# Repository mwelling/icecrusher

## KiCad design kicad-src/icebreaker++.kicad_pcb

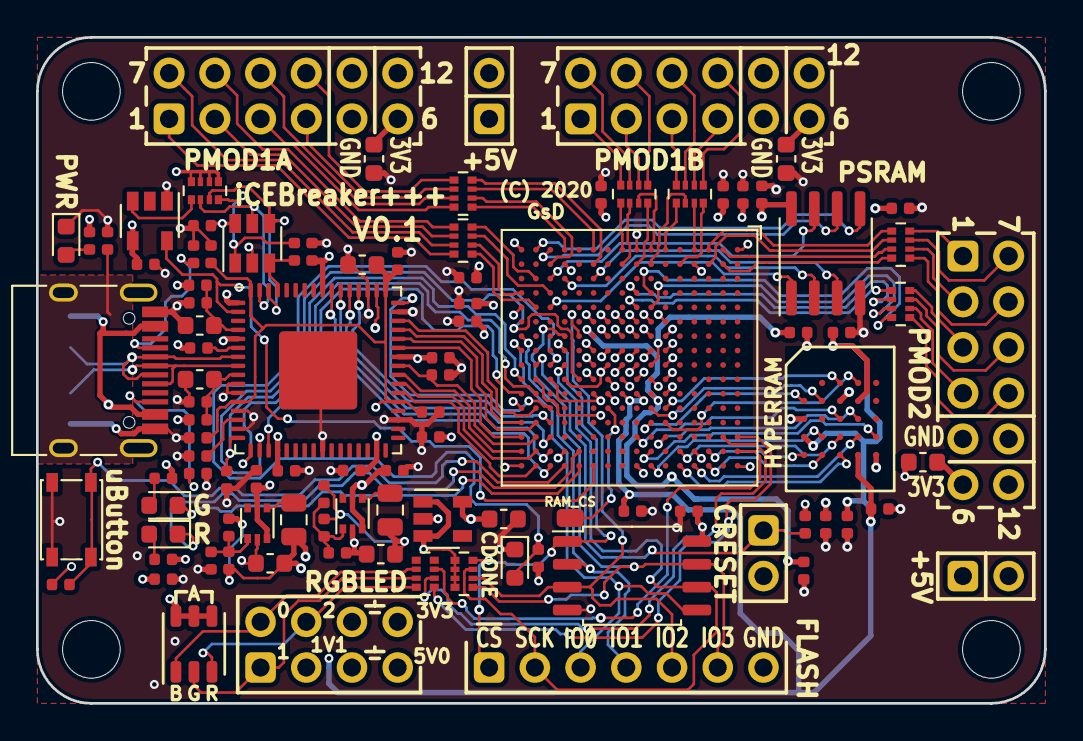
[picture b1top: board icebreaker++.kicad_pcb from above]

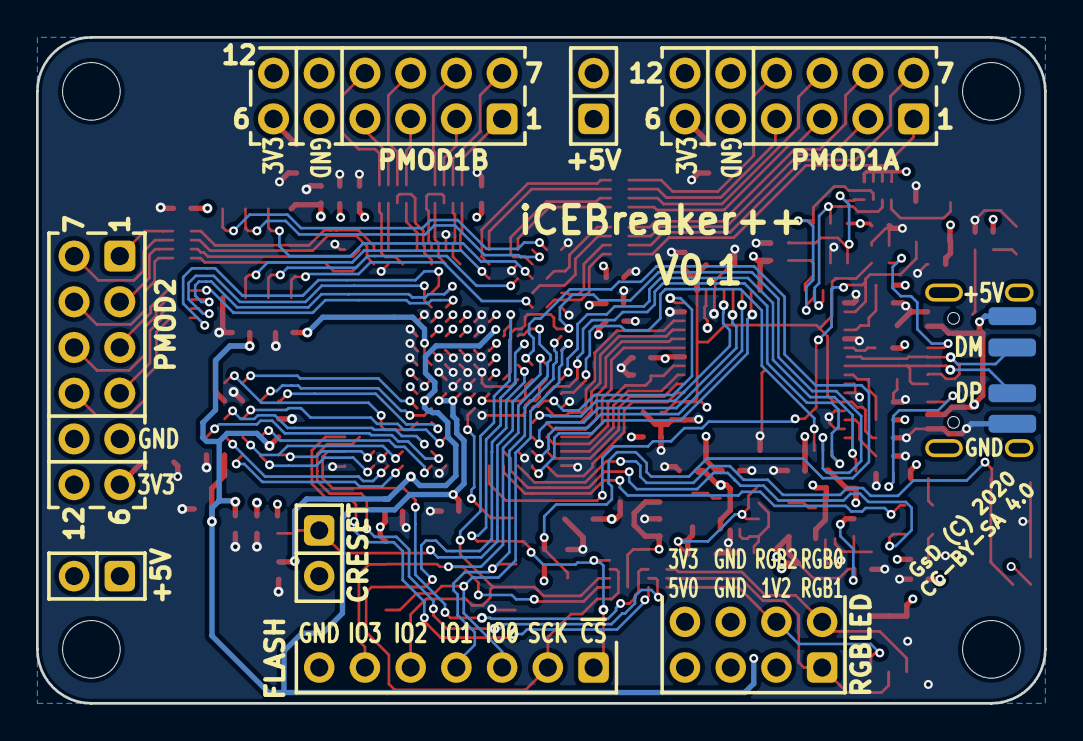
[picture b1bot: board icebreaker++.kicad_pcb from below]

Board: 4 copper layers, 56.0 x 37.0 mm, 104 parts (4 on the bottom side), 130 nets.

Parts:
C1, C4, C10, C12, C13, C14, C16, C17, C18, C19, C20, C21, C22: 100n; C_0402_1005Metric
C2, C3, C5, C8, C11, C35, C36, C37, C38, C39, C40, C41, C42, C43: 0.1uF; C_0402_1005Metric
C6, C7, C9: 4u7; C_0603_1608Metric
C15, C23: 4.7uF; C_0402_1005Metric
C24, C28, C29: 10uF; C_0603_1608Metric
C25, C30, C31: 1uF; C_0402_1005Metric
C26, C27: 6.8pF; C_0402_1005Metric
C32, C33, C34: DNP; C_0603_1608Metric
D1, D4: GRN; LED_0603_1608Metric
D3: BLU; LED_0603_1608Metric
D5: RED; LED_0603_1608Metric
D11: LED_RGB; LED_Cree_PLCC6_3.4x3.4mm
J20: Flash; PinHeader_1x07_P2.54mm_Vertical
J21, J23, J27: PMOD; PMOD_Angled_2x06
J22, J26: 5V AUX; PinHeader_2x01_P2.54mm_Vertical
J24: USB_C_Receptacle_USB2.0; USB_C_Receptacle_HRO_TYPE-C-31-M-12
J25: RGB Led; PinHeader_2x04_P2.54mm_Vertical
J28: CRESET; PinHeader_2x01_P2.54mm_Vertical
L1, L2: 600; L_0402_1005Metric
L3, L4: 2.2uH; L_0805_2012Metric
P2, P3, P4, P5: UP; PAD_SMD_1x2.65
P6: RAM_CS; PAD_SMD_1x1.5
R1: 1M; R_0402_1005Metric
R2, R11: 10k; R_Array_Convex_4x0402
R3, R4, R7, R16, R17, R18, R27: 33R; R_Array_Convex_4x0402
R5, R14, R15: 330E; R_0402_1005Metric
R6, R12: 2k2; R_0402_1005Metric
R8: 12k; R_0402_1005Metric
R9, R13, R19, R25: 10k; R_0402_1005Metric
R10: 210k; R_0402_1005Metric
R20: 1k; R_0402_1005Metric
R21, R22: 5.1k; R_0402_1005Metric
R23: 47k; R_0402_1005Metric
R24: 84k5; R_0402_1005Metric
R26: 100k; R_0402_1005Metric
SW1: TACT; SW_SPST_PTS810
U1: 93C46B-SOT-23-6; SOT-23-6
U2: FT2232H; QFN-64-1EP_9x9mm_P0.5mm_EP4.35x4.35mm
U3: W25Q32JVSS; SOIC-8_5.23x5.23mm_P1.27mm
U4, U5: TLV62569DRL; SOT-666
U6: TLV713285PDBV; SOT-23-5
U7: 12MHz; SOT-23-5
U8: ECP5U-12-CABGA256; BGA-256_14.0x14.0mm_Layout16x16_P0.8mm_Ball0.45mm_Pad0.32mm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
U9: LY68L6400SLIT; SOIC-8_3.9x4.9mm_P1.27mm
U10: IS66WVH16M8ALL; BGA-24_8.0x6.0mm_Layout5x5_P0.8mm_Pad0.35mm_NSMD

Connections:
+1V1: C27.1, C29.1, C31.1, C35.1, C36.1, C37.1, C38.1, L4.2, R24.2, U8.G6 (VCC[6]), U8.G7 (VCC[6]), U8.G9 (VCC[6]), U8.L8 (VCC[6]), U8.L9 (VCC[6]), U8.L10 (VCC[6])
+1V8: C7.1, C8.1, C10.1, C14.1, C16.1, C17.1, C40.1, C41.1, C42.1, U2.12 (VCORE), U2.37 (VCORE), U2.49 (VREGOUT), U2.64 (VCORE), U8.H11 (VCCIO2[2]), U8.J11 (VCCIO2[2]), U10.B4 (VCC), U10.D1 (VCCQ), U10.E4 (VCCQ)
+2V5: C24.1, C25.1, U6.5 (OUT), U8.G11 (VCCAUX[2]), U8.L7 (VCCAUX[2])
+3V3: C1.1, C2.1, C3.1, C4.1, C5.1, C11.1, C18.1, C19.1, C20.1, C21.1, C22.1, C26.1, C28.1, C30.1, C32.2, C33.2, C34.2, C39.1, C43.1, D11.4 (BA), D11.5 (GA), D11.6 (RA), J21.6, J21.12, J23.6, J23.12, J25.8, J27.6, J27.12, L1.1, L2.1, L3.2, R2.5, R2.6, R2.7, R2.8, R5.1, R9.2, R10.2, R11.1, R11.2, R11.3, R11.4, R12.1, R13.2, R14.2, R15.2, R19.1, U1.6 (VCC), U2.20 (VCCIO), U2.31 (VCCIO), U2.42 (VCCIO), U2.50 (VREGIN), U2.56 (VCCIO), U3.8 (VCC), U6.1 (IN), U6.3 (EN), U7.4 (VDD), U8.F10 (VCCIO1[2]), U8.F11 (VCCIO1[2]), U8.H6 (VCCIO7[2]), U8.H7 (VCCIO7[2]), U8.J6 (VCCIO6[2]), U8.J7 (VCCIO6[2]), U8.K11 (VCCIO3[2]), U8.L6 (VCCIO8), U8.L11 (VCCIO3[2]), U8.P10 (CFG_1), U9.8 (VCC)
+5V: C15.1, C23.1, J22.1, J24.A4 (VBUS), J24.A9 (VBUS), J24.B4 (VBUS), J24.B9 (VBUS), J25.7, J26.1, P2.1 (PAD), U4.3 (VIN), U4.5 (EN), U5.3 (VIN), U5.5 (EN)
/DONE: D3.2 (A), R12.2, U8.P9 (DONE)
/FLASH_CS: J20.1, R11.8, U3.1 (~CS), U8.N8 (PB15A/+/HOLDN/DI/BUSY/CSSPIN/CEN)
/FLASH_MISO|IO1: J20.4, U3.2 (DO(IO1)), U8.T7 (PB11A/+/D1/MISO/IO1)
/FLASH_MOSI|IO0: J20.3, U3.5 (DI(IO0)), U8.T8 (PB11B/-/D0/MOSI/IO0)
/FLASH_SCK: J20.2, R11.7, U3.6 (CLK), U8.N9 (CCLK/MCLK/SCK)
/FLASH_~HLD~|~RST~|IO3: J20.6, R11.5, U3.7 (IO3), U8.N7 (PB9A/+/D3/IO3)
/FLASH_~WP~|IO2: J20.5, R11.6, U3.3 (IO2), U8.M7 (PB9B/-/D2/IO2)
/FTDI_CLK: U2.2 (OSCI), U7.5 (OUT), U8.L16 (PR26A/+/PCLKT3_1/HS/RDQ32)
/JTAG_TCK: R20.1, U2.16 (ADBUS0), U8.T10 (TCK)
/JTAG_TDI: U2.17 (ADBUS1), U8.R11 (TDI)
/JTAG_TDO: U2.18 (ADBUS2), U8.M10 (TDO)
/JTAG_TMS: U2.19 (ADBUS3), U8.T11 (TMS)
/PMODS/P1A1: R16.5, U8.R5 (PL44A/+/HS/LDQS44)
/PMODS/P1A1x: J23.1, R16.4
/PMODS/P1A2: R16.7, U8.P4 (PL41A/+/HS/LDQ44)
/PMODS/P1A2x: J23.2, R16.2
/PMODS/P1A3: R3.5, U8.N1 (PL32A/+/HS/LDQS32)
/PMODS/P1A3x: J23.3, R3.4
/PMODS/P1A4: R3.7, U8.L1 (PL26A/+/PCLKT6_1/HS/LDQ32)
/PMODS/P1A4x: J23.4, R3.2
/PMODS/P1A7: R16.6, U8.T4 (PL44B/-/HS/LDQSN44)
/PMODS/P1A7x: J23.7, R16.3
/PMODS/P1A8: R16.8, U8.R3 (PL41B/-/HS/LDQ44)
/PMODS/P1A8x: J23.8, R16.1
/PMODS/P1A9: R3.6, U8.P2 (PL32B/-/HS/LDQSN32)
/PMODS/P1A9x: J23.9, R3.3
/PMODS/P1A10: R3.8, U8.L2 (PL26B/-/PCLKC6_1/HS/LDQ32)
/PMODS/P1A10x: J23.10, R3.1
/PMODS/P1B1: R4.1, U8.J1 (PL23A/+/PCLKT7_1/HS/LDQ20)
/PMODS/P1B1x: J27.1, R4.8
/PMODS/P1B2: R4.3, U8.G1 (PL20A/+/GR_PCLK7_1/HS/LDQS20)
/PMODS/P1B2x: J27.2, R4.6
/PMODS/P1B3: R17.1, U8.F1 (PL14A/+/HS/LDQ20)
/PMODS/P1B3x: J27.3, R17.8
/PMODS/P1B4: R17.3, U8.D1 (PL8A/+/HS/LDQS8)
/PMODS/P1B4x: J27.4, R17.6
/PMODS/P1B7: R4.2, U8.J2 (PL23B/-/PCLKC7_1/HS/LDQ20)
/PMODS/P1B7x: J27.7, R4.7
/PMODS/P1B8: R4.4, U8.H2 (PL20B/-/HS/LDQSN20)
/PMODS/P1B8x: J27.8, R4.5
/PMODS/P1B9: R17.2, U8.G2 (PL14B/-/HS/LDQ20)
/PMODS/P1B9x: J27.9, R17.7
/PMODS/P1B10: R17.4, U8.E2 (PL8B/-/HS/LDQSN8)
/PMODS/P1B10x: J27.10, R17.5
/PMODS/P2_1: R7.1, U8.C1 (PL5A/+/HS/LDQ8)
/PMODS/P2_1x: J21.1, R7.8
/PMODS/P2_2: R7.3, U8.B1 (PL2A/+/HS/LDQ8)
/PMODS/P2_2x: J21.2, R7.6
/PMODS/P2_3: R18.1, U8.H5 (PL17A/+/HS/LDQ20)
/PMODS/P2_3x: J21.3, R18.8
/PMODS/P2_4: R18.3, U8.G5 (PL11A/+/HS/LDQ8)
/PMODS/P2_4x: J21.4, R18.6
/PMODS/P2_7: R7.2, U8.C2 (PL5B/-/HS/LDQ8)
/PMODS/P2_7x: J21.7, R7.7
/PMODS/P2_8: R7.4, U8.B2 (PL2B/-/HS/LDQ8)
/PMODS/P2_8x: J21.8, R7.5
/PMODS/P2_9: R18.2, U8.H4 (PL17B/-/HS/LDQ20)
/PMODS/P2_9x: J21.9, R18.7
/PMODS/P2_10: R18.4, U8.G4 (PL11B/-/HS/LDQ8)
/PMODS/P2_10x: J21.10, R18.5
/PMODS/RAM_CLK: U8.P1 (PL35A/+/HS/LDQ32), U9.6 (CLK)
/PMODS/RAM_CS: U8.P5 (PL47D/-/LLC_GPLL0C_IN/LDQ44), U9.1 (~CS)
/PMODS/RAM_IO0: U8.R1 (PL35B/-/VREF1_6/HS/LDQ32), U9.5 (DI(IO0))
/PMODS/RAM_IO1: U8.N3 (PL35D/-/LDQ32), U9.2 (DO(IO1))
/PMODS/RAM_IO2: U8.L3 (PL32C/+/LDQ32), U9.3 (IO2)
/PMODS/RAM_IO3: U8.P3 (PL38B/-/HS/LDQ44), U9.7 (IO3)
/PROGRAMn: J28.1, R19.2, U8.R9 (PROGRAMN)
/RAM/HRAM_CLK: U8.G12 (PR11A/+/HS/RDQ8), U10.B2 (CK)
/RAM/HRAM_CLK#: U8.G13 (PR11B/-/HS/RDQ8), U10.B1 (CK#)
/RAM/HRAM_CS: U8.F12 (PR8D/-/RDQ8), U10.A3 (CS#)
/RAM/HRAM_DQ0: U8.E15 (PR8B/-/HS/RDQSN8), U10.D3 (DQ0)
/RAM/HRAM_DQ1: U8.G16 (PR20A/+/GR_PCLK2_1/HS/RDQS20), U10.D2 (DQ1)
/RAM/HRAM_DQ2: U8.F14 (PR5D/-/RDQ8), U10.C4 (DQ2)
/RAM/HRAM_DQ3: U8.D16 (PR8A/+/HS/RDQS8), U10.D4 (DQ3)
/RAM/HRAM_DQ4: U8.G15 (PR14B/-/HS/RDQ20), U10.D5 (DQ4)
/RAM/HRAM_DQ5: U8.E16 (PR11D/-/RDQ8), U10.E3 (DQ5)
/RAM/HRAM_DQ6: U8.C16 (PR5A/+/HS/RDQ8), U10.E2 (DQ6)
/RAM/HRAM_DQ7: U8.C15 (PR5B/-/HS/RDQ8), U10.E1 (DQ7)
/RAM/HRAM_RST: U8.F13 (PR8C/+/RDQ8), U10.A4 (RESET#)
/RAM/HRAM_RWDS: U8.H14 (PR14D/-/RDQ20), U10.C3 (RWDS)
/RAM_CS: P6.1 (PAD), U8.K12 (PR29B/-/HS/RDQ32)
/USB_DM: J24.A7 (D-), J24.B7 (D-), P3.1 (PAD), U2.7 (DM)
/USB_DP: J24.A6 (D+), J24.B6 (D+), P4.1 (PAD), U2.8 (DP)
/shield: J24.S1 (SHIELD), R1.2
/xFIFO_D0: U2.38 (BDBUS0), U8.R16 (PR35B/-/VREF1_3/HS/RDQ32)
/xFIFO_D1: U2.39 (BDBUS1), U8.R15 (PR38C/+/RDQ44)
/xFIFO_D2: U2.40 (BDBUS2), U8.T15 (PR38D/-/RDQ44)
/xFIFO_D3: R25.1, U2.41 (BDBUS3), U8.R14 (PR41B/-/HS/RDQ44)
/xFIFO_D4: U2.43 (BDBUS4), U8.T14 (PR41D/-/RDQ44)
/xFIFO_D5: U2.44 (BDBUS5), U8.R13 (PR41C/+/RDQ44)
/xFIFO_D6: U2.45 (BDBUS6), U8.T13 (PR44B/-/HS/RDQSN44)
/xFIFO_D7: U2.46 (BDBUS7), U8.R12 (PR44A/+/HS/RDQS44)
/xFIFO_WKUP: U2.55 (BCBUS4), U8.P16 (PR35A/+/HS/RDQ32)
/xFIFO_~RD: U2.53 (BCBUS2), U8.P14 (PR38B/-/HS/RDQ44)
/xFIFO_~RXF: U2.48 (BCBUS0), U8.P12 (PR47D/-/LRC_GPLL0C_IN/RDQ44)
/xFIFO_~TXE: U2.52 (BCBUS1), U8.P13 (PR41A/+/HS/RDQ44)
/xFIFO_~WR: U2.54 (BCBUS3), U8.P15 (PR32B/-/HS/RDQSN32)
/~BUTTON: R13.1, SW1.1, U8.N16 (PR32A/+/HS/RDQS32)
/~LEDG: D4.1 (K), U8.M16 (PR26C/+/PCLKT3_0/RDQ32)
/~LEDR: D5.1 (K), U8.M15 (PR26D/-/PCLKC3_0/RDQ32)
/~LED_RGB0: D11.1 (RK), J25.2, R27.2
/~LED_RGB1: D11.2 (GK), J25.1, R27.3
/~LED_RGB2: D11.3 (BK), J25.4, R27.4
GND: C1.2, C2.2, C3.2, C4.2, C5.2, C6.2, C7.2, C8.2, C9.2, C10.2, C11.2, C12.2, C13.2, C14.2, C15.2, C16.2, C17.2, C18.2, C19.2, C20.2, C21.2, C22.2, C23.2, C24.2, C25.2, C28.2, C29.2, C30.2, C31.2, C32.1, C33.1, C34.1, C35.2, C36.2, C37.2, C38.2, C39.2, C40.2, C41.2, C42.2, C43.2, D1.1 (K), D3.1 (K), J20.7, J21.5, J21.11, J22.2, J23.5, J23.11, J24.A1 (GND), J24.A12 (GND), J24.B1 (GND), J24.B12 (GND), J25.5, J25.6, J26.2, J27.5, J27.11, J28.2, P5.1 (PAD), R1.1, R8.2, R20.2, R21.1, R22.1, R23.1, R25.2, R26.1, SW1.2, U1.2 (VSS), U2.1 (GND), U2.5 (GND), U2.10 (AGND), U2.11 (GND), U2.13 (TEST), U2.15 (GND), U2.25 (GND), U2.35 (GND), U2.47 (GND), U2.51 (GND), U2.65, U3.4 (GND), U4.2 (GND), U5.2 (GND), U6.2 (GND), U7.1 (GND), U8.A1 (GND[27]), U8.A16 (GND[27]), U8.D2 (GND[27]), U8.D15 (GND[27]), U8.F6 (VCCIO0[2]), U8.F7 (VCCIO0[2]), U8.F8 (GND[27]), U8.F9 (GND[27]), U8.G8 (GND[27]), U8.G10 (GND[27]), U8.H1 (GND[27]), U8.H8 (GND[27]), U8.H9 (GND[27]), U8.H10 (GND[27]), U8.H16 (GND[27]), U8.J8 (GND[27]), U8.J9 (GND[27]), U8.J10 (GND[27]), U8.K6 (GND[27]), U8.K7 (GND[27]), U8.K8 (GND[27]), U8.K9 (GND[27]), U8.K10 (GND[27]), U8.N2 (GND[27]), U8.N10 (CFG_0), U8.N15 (GND[27]), U8.R10 (CFG_2), U8.T1 (GND[27]), U8.T5 (GND[27]), U8.T12 (GND[27]), U8.T16 (GND[27]), U9.4 (GND), U10.B3 (VSS), U10.C1 (VSSQ), U10.E5 (VSSQ)
unnamed: C6.1, C12.1, L2.2, U2.4 (VPHY)
unnamed: C9.1, C13.1, L1.2, U2.9 (VPLL)
unnamed: C26.2, R10.1, R23.2, U4.1 (FB)
unnamed: C27.2, R24.1, R26.2, U5.1 (FB)
unnamed: D1.2 (A), R5.2
unnamed: D4.2 (A), R14.1
unnamed: D5.2 (A), R15.1
unnamed: J24.A5 (CC1), R21.2
unnamed: J24.B5 (CC2), R22.2
unnamed: L3.1, U4.4 (SW)
unnamed: L4.1, U5.4 (SW)
unnamed: R2.1, U7.3 (OE/~ST~/NC)
unnamed: R2.2, U1.5 (CS), U2.63 (EECS)
unnamed: R2.3, U1.4 (CLK), U2.62 (EECLK)
unnamed: R2.4, R6.2, U1.1 (DO)
unnamed: R6.1, U1.3 (DI), U2.61 (EEDATA)
unnamed: R8.1, U2.14 (~RESET)
unnamed: R9.1, U2.6 (REF)
unnamed: R27.5, U8.A14 (PT65B/-)
unnamed: R27.7, U8.A15 (PT67B/-)
unnamed: R27.6, U8.B14 (PT67A/+)

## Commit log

2020-12-13 Initial commit
    Changes made to the icebreaker++-ram design from Greg's advent calendar before posting to OSHPark.

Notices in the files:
kicad-src/icebreaker++.kicad_pcb:
License: CC-BY-SA 4.0
GsD (C) 2020
CC-BY-SA 4.0
(C) 2020
